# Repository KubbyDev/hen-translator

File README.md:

# Hen Translator

The goal of this project is to make a small module that can be attached around the neck of a chicken. This module listens for chicken sounds and "translates" them (it says a random sentence with a synthesized voice).
This idea is dumb, I know, but I learned a lot doing it.

## Demo

## Things I should change

- The main problem in this design is the lack of some kind of sound recognition. Just looking at the sound level is not enough to trigger the translation only when the chicken makes noises. I originally planned to try to use FFTs to make a simple recognition system but the AtMega328p is too underpowered and has far too little memory to work with. If I make a V2, I will probably go for a much more powerful STM32 or even a Linux system.
- The speaker is not powerful enough. This should be fairly easy to change but I have to keep in mind that it will also draw more power.

## How does it work?

### Electronics

I made my own PCB for this project. The main concerns when selecting the components were size, power consumption and cost.
All the components I used on the final board are listed here:
<https://github.com/KubbyDev/hen-translator/blob/main/Infos/Components.txt>

##### Storage

To store all the audio samples, I decided to use an SD card because it's easy to load new wave files. I used a mosfet to cut power when the SD card is not needed because the board is just listening most of the time.

##### Speaker

I used a simple 8 Ohm 0.7 Watt smd speaker to produce sounds. I added a large capacitor to filter out current spikes and a mosfet so the microcontroller can control it without powering it.

##### Microcontroller

At the beginning of the project I wanted to use an Arduino Nano because I was familiar with these boards. The main problem was its size. But then I heard about the Pro Mini which is much smaller. The only catch is that it doesn't have a USB port for programming, but it's not that hard to do without. Then I did some research and saw that it's a good idea to desolder the power led and the 3.3V LDO if I don't use them because they draw power. Ok why not. But then it's easier to just buy the microcontroller and solder it into my own board. The only difficulty it adds is the bootloader that doesn't come preinstalled.

So I chose an AtMega328p, and I added through-hole test points to plug wires to burn the bootloader (SPI) and load programs (Serial). I also added a switch between the power pins of the MCU and the power rail of the rest of the board because it's 3.3V and I want to be able to program it with an Arduino (5V) without putting 5V in the 3.3V components.

My first attempt at burning the bootloader didn't work because I was using the Arduino Uno bootloader but the 1st version of the PCB was using a 10 MHz crystal oscillator. This didn't cause problems to burn the bootloader because SPI is synchronous, but then I couldn't upload sketches because the baud rates were wrong. I solved this by simply using the 8 MHz internal clock instead of my 10 MHz external crystal, and burning a bootloader made for an 8 MHz clock. I could hack a 10 MHz bootloader but now that I know the external crystal is not needed, I prefer just removing it.

##### Power management

My first idea was to use a 3V button battery and a boost converter to get 5V to power the microcontroller. But I wanted to use an SD card which works at 3.3V, so I had to add a 3.3V LDO from 5V or a second boost converter. This is not efficient at all.
But then I saw that the AtMega328p works from 1.8V to 5.5V, so I decided to use a single boost converter to 3.3V and power everything from it. I also did some research about low voltage mode (1.8V) on SD cards but didn't find much information and it seemed like I would still have to start at 3.3V to then switch to 1.8V so I gave up this idea.

Later I realized I had another problem: the speaker draws 200 mA at 3.3V which a button battery can't provide. So I switched to a 1.5V AAA battery. But 200mA is also too much for the cheap boost converter I had found, and better boost converters are a lot more expensive. So I just connected the speaker directly to the battery so I don't need to change the converter (I had already ordered it), I can remove the resistor I had to limit current at 3.3V and I can have a higher current than if I chose a cheap regulator that I would have to run at its limits (so with a low efficiency). With this solution I get 0.3W at 1.5V.

I could switch to two 1/2 AAA 1.2V batteries. They take the same space as the 1.5V battery but have a combined output of 2.4V which forces 0.7W to pass through the speaker. But they are very expensive and the small increase in volume is not worth it.

##### Crystal oscillator

To provide a clock to the microcontroller I wanted to use a 16 MHz quartz oscillator at first because it's what's used on Uno and Nano boards. But when I chose to power everything from 3.3V I saw that the AtMega328p has a maximum clock speed that depends on the power input voltage. At 3.3V, 16 MHz is too fast, but 10 MHz should work fine so I used a 10 MHz external oscillator.

Then, because of the bootloader problems described in the microcontroller section, I just removed it to use the internal 8 MHz oscillator.

##### Microphone

I chose a MEMS microphone because they are cheap and very small. For the first version of the PCB I chose a PDM microphone without doing much research about it and found out later that it's very hard to read PDM from an AtMega328p...

I did a lot of research and found solutions like hacking the SPI controller to read PDM with it, using a DAC to convert PDM to analog to read it, using a low pass filter to filter out low SPL values and just triggering the translation when something comes out of the filter etc...

Eventually I just changed the PDM microphone for an analog output microphone with an operational amplifier. It was a nightmare to solder but it works well.

##### PCB

The first PCB had some major flaws like the microphone I couldn't read, the speaker that drew too much current and some pullup resistors that were missing on the SPI lines for the SD card. I also connected Aref to VCC instead of a capacitor to GND on the microcontroller.

The test points were too small for my wires, so I had to solder them but some of the vias detached and everything was a big mess, but I was able to learn from it and I haven't had any problem with the second version of the PCB.

### Software

To burn the bootloader, I use an Arduino Uno with the ArduinoISP example sketch connected via SPI to my PCB. To upload sketches, I use an Arduino Uno with the microcontroller removed and a Serial connection to my PCB. The procedure is detailed here:
<https://github.com/KubbyDev/hen-translator/blob/main/Infos/BurnBootloader.txt>

The program has 3 things to do:

- listen for chicken sounds
- when it detects one, play a random wav file from the SD card
- monitor the battery voltage and alert with the led or the speaker when power is too low

##### Speaker control

To play wav files I use the TMRpcm library. It's easy to use because my use case is standard.

##### SD card reading

To read data from the SD card I use the Arduino SD library (and TMRpcm does too). It works with standard 2GB SD cards but not with the cheap 512B cards I bought. I will try to fix the library but for now I just use 2GB cards.

##### Microphone reading

I would like to do some cool FFT sound recognition but I don't think it will be possible on the AtMega328p mainly because it's too slow and doesn't have enough ram.
For the moment I will just trigger the translation when the sound pressure level goes higher than a certain threshold.

### Mechanics

I had to learn Fusion360 for this project so the CAD could probably be way better, but it works.
There are two parts. The box that goes on the chicken, and a stand because I don't actually have a chicken at home and also because this version is not reliable enough for these conditions.
Everything is 3D printed in white PLA and painted.

The collar is just a box holding the board and the battery with a power switch and holes for sound to come in and out.

The stand is based on a chicken I found on Thingyverse. The interior is hollow, and contains a PCB (the same PCB, but without microphone because it's not needed), a battery, a power switch and a button to trigger a chicken sound. The button is an end of travel sensor that we can trigger by pushing on the thingy on the head of the chicken.

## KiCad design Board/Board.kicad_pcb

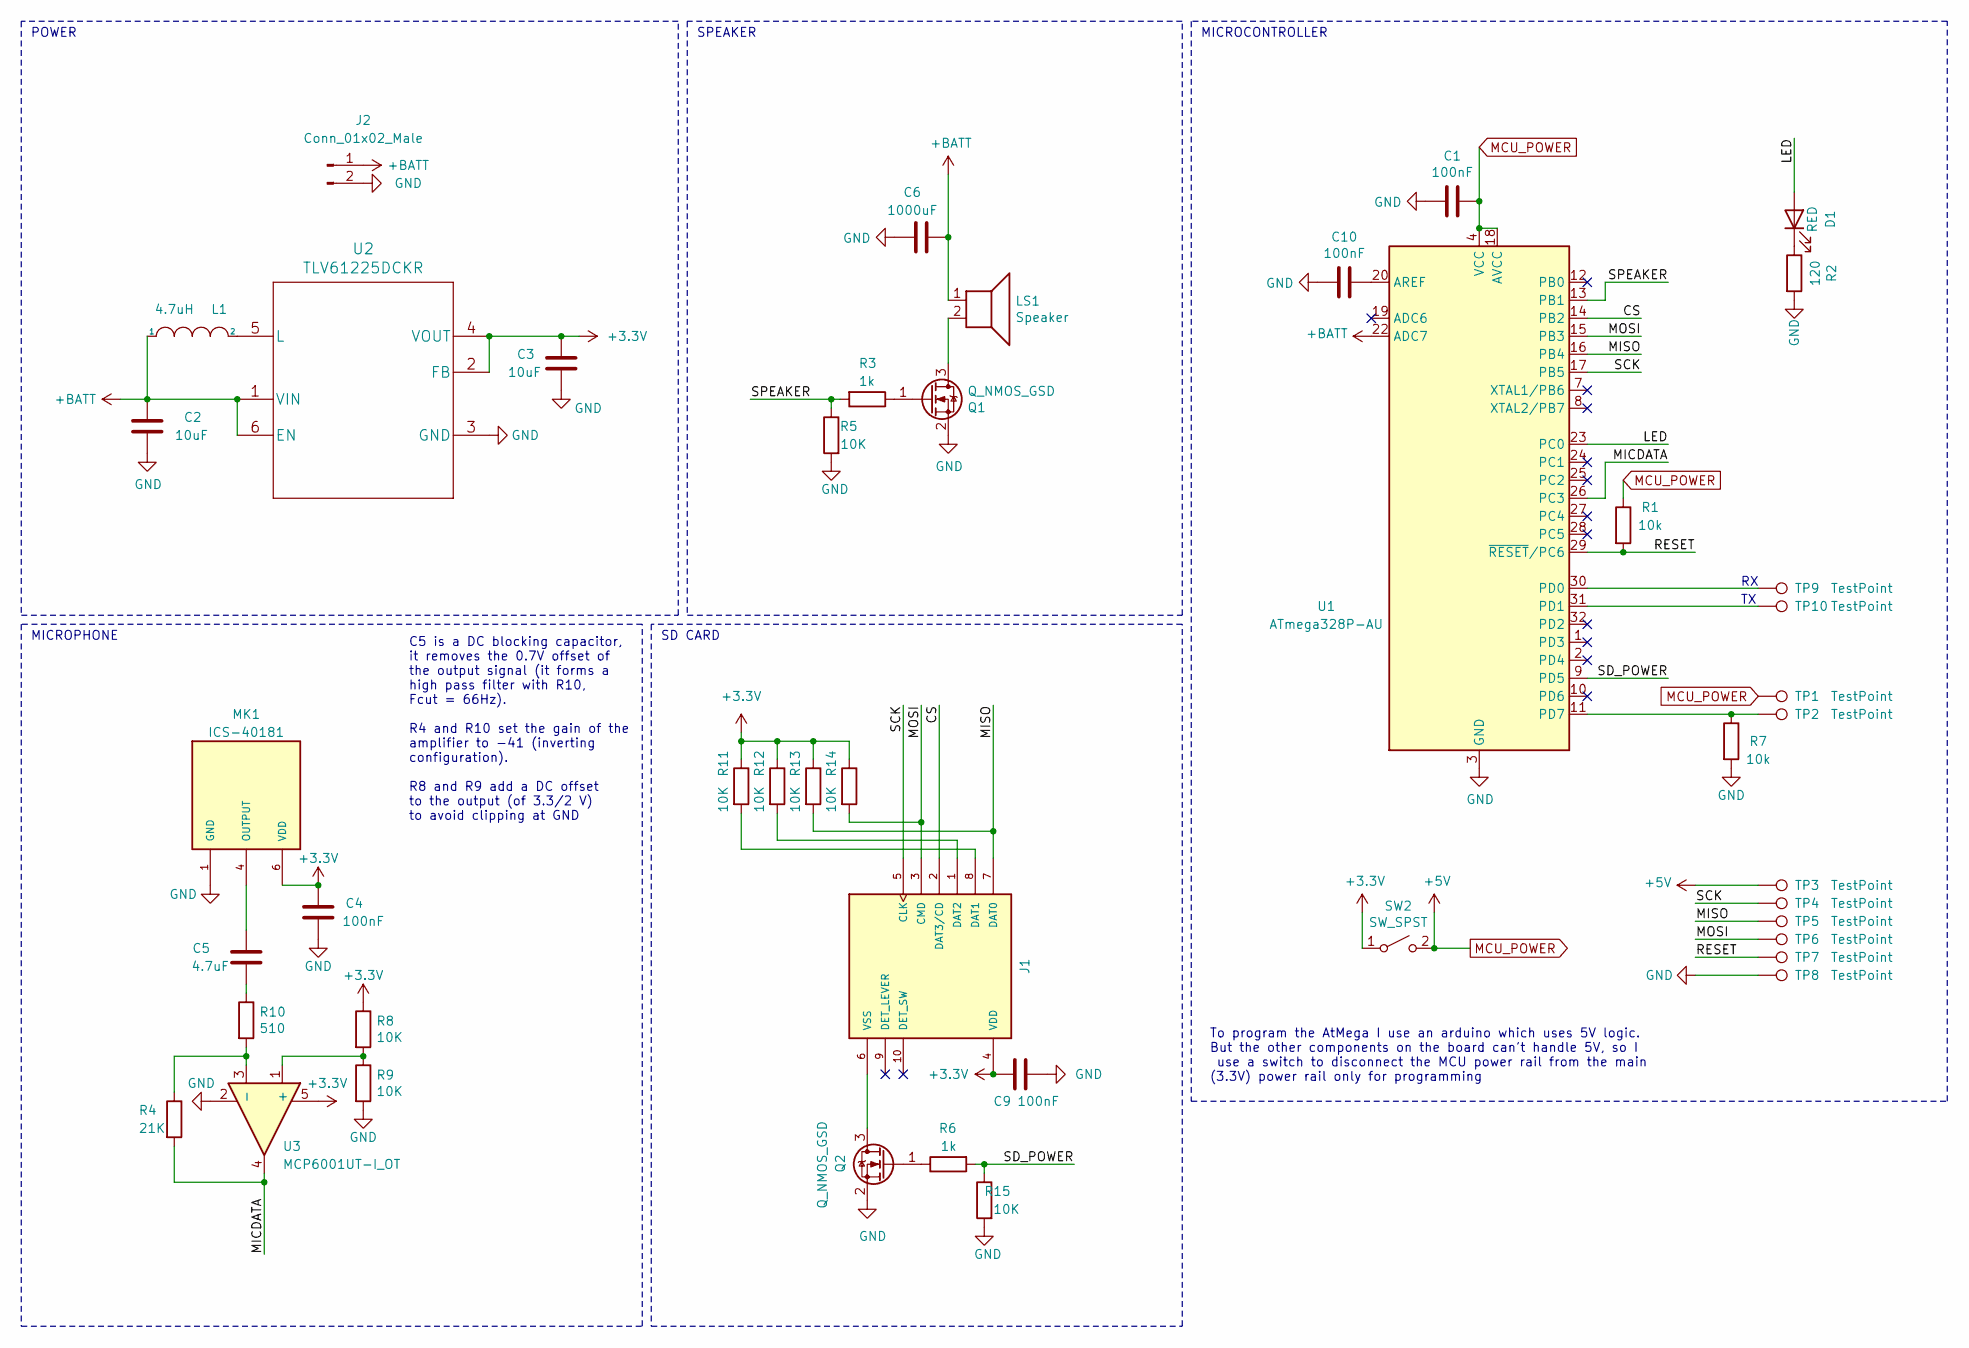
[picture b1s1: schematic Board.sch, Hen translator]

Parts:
C1, C4, C9, C10: 100nF; C_0603_1608Metric
C2, C3: 10uF; C_0805_2012Metric
C5: 4.7uF; C_0603_1608Metric
C6: 1000uF; C_Radial_D8.0mm_H11.5mm_P3.50mm
D1: RED; LED_0805_2012Metric
J1: 5025700893; MOLEX_5025700893
J2: Conn_01x02_Male; S02B-PASK
L1: 4.7uH; L_1008_2520Metric
LS1: Speaker; SPKR_CMS-151135-078S-67
MK1: ICS-40181; MIC_ICS-40181
Q1, Q2: Q_NMOS_GSD; SOT-23
R1, R7: 10k; R_0603_1608Metric
R2: 120; R_0603_1608Metric
R3, R6: 1k; R_0603_1608Metric
R4: 21K; R_0603_1608Metric
R5, R8, R9, R11, R12, R13, R14, R15: 10K; R_0603_1608Metric
R10: 510; R_0603_1608Metric
SW2: SW_SPST; SW_DIP_SPSTx01_Slide_6.7x4.1mm_W7.62mm_P2.54mm_LowProfile
TP1, TP2, TP3, TP4, TP5, TP6, TP7, TP8, TP9, TP10: TestPoint; TestPoint_THTPad_D1.0mm_Drill0.7mm
U1: ATmega328P-AU; TQFP-32_7x7mm_P0.8mm
U2: TLV61225DCKR; SOT65P210X110-6N
U3: MCP6001UT-I_OT; SOT95P270X145-5N

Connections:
+3V3: C3.1, C4.1, C9.1, J1.4 (VDD), MK1.6 (VDD), R8.1, R11.1, R12.1, R13.1, R14.1, SW2.1 (A), U2.2 (FB), U2.4 (VOUT), U3.5
+BATT: C2.1, C6.1, J2.1, L1.1, LS1.1, U1.22 (ADC7), U2.1 (VIN), U2.6 (EN)
/CS: J1.2 (DAT3/CD), U1.14 (PB2)
/LED: D1.2 (A), U1.23 (PC0)
/MICDATA: R4.2, U1.26 (PC3), U3.4
/MISO: J1.7 (DAT0), R13.2, TP5.1, U1.16 (PB4)
/MOSI: J1.3 (CMD), R14.2, TP6.1, U1.15 (PB3)
/RESET: R1.2, TP7.1, U1.29 (~RESET~/PC6)
/SCK: J1.5 (CLK), TP4.1, U1.17 (PB5)
/SD_POWER: R6.2, R15.1, U1.9 (PD5)
/SPEAKER: R3.2, R5.1, U1.13 (PB1)
GND: C1.2, C2.2, C3.2, C4.2, C6.2, C9.2, C10.2, J2.2, MK1.1 (GND), MK1.2 (GND), MK1.3 (GND), MK1.5 (GND), Q1.2 (S), Q2.2 (S), R2.2, R5.2, R7.2, R9.2, R15.2, TP8.1, U1.3 (GND), U1.5 (GND), U1.21 (GND), U2.3 (GND), U3.2
MCU_POWER: C1.1, R1.1, SW2.2 (B), TP1.1, TP3.1, U1.4 (VCC), U1.6 (VCC), U1.18 (AVCC)
unnamed: C5.1, MK1.4 (OUTPUT)
unnamed: C5.2, R10.1
unnamed: C10.1, U1.20 (AREF)
unnamed: D1.1 (K), R2.1
unnamed: J1.1 (DAT2), R12.2
unnamed: J1.6 (VSS), Q2.3 (D)
unnamed: J1.8 (DAT1), R11.2
unnamed: L1.2, U2.5 (L)
unnamed: LS1.2, Q1.3 (D)
unnamed: Q1.1 (G), R3.1
unnamed: Q2.1 (G), R6.1
unnamed: R7.1, TP2.1, U1.11 (PD7)
unnamed: R8.2, R9.1, U3.1 (+)
unnamed: R4.1, R10.2, U3.3 (-)
unnamed: TP9.1, U1.30 (PD0)
unnamed: TP10.1, U1.31 (PD1)

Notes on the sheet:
POWER
SD CARD
MICROPHONE
SPEAKER
MICROCONTROLLER
C5 is a DC blocking capacitor, it removes the 0.7V offset of the output signal (it forms a high pass filter with R10, Fcut = 66Hz). R4 and R10 set the gain of the amplifier to -41 (inverting configuration). R8 and R9 add a DC offset to the output (of 3.3/2 V) to avoid clipping at GND
To program the AtMega I use an arduino which uses 5V logic. But the other components on the board can't handle 5V, so I use a switch to disconnect the MCU power rail from the main (3.3V) power rail only for programming

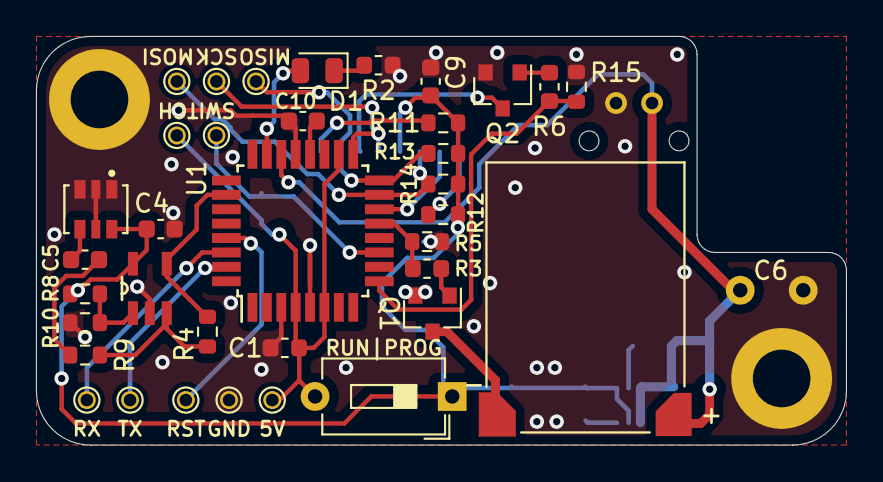
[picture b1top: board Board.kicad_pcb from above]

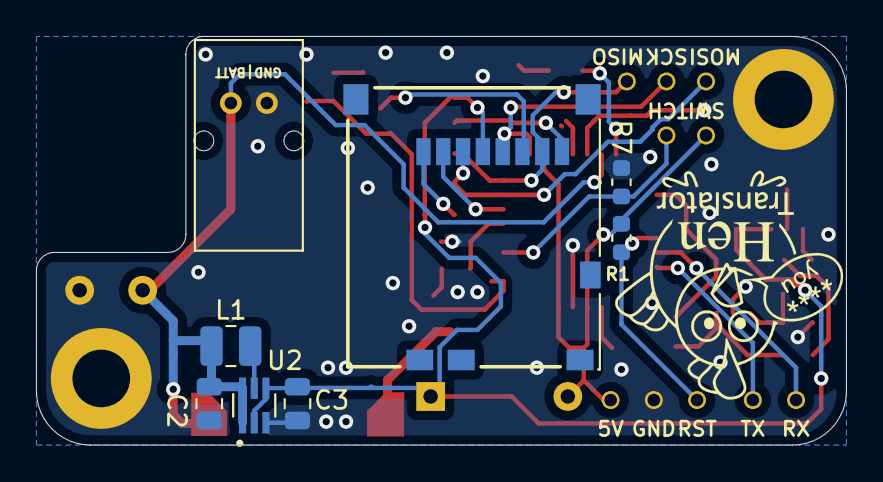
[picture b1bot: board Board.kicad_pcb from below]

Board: 2 copper layers, 45.0 x 22.7 mm, 45 parts (8 on the bottom side), 29 nets.

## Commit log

2021-01-24 Some research
2021-01-25 Switched to 3.3V
2021-01-26 Started schematic
2021-01-29 Schematic and BOM almost done
2021-02-05 Schematic done, components almost selected
2021-02-07 BOM ready
2021-02-07 Changed components + first layout tests
2021-02-09 First PCB
2021-02-09 PCB almost done
2021-02-09 Replaced SD connector by correct one
2021-02-10 Started enclosure
2021-02-10 Board done :)
2021-02-18 Enclosure almost finished
2021-02-25 Enclosure added handles
2021-02-25 Fourrier tests
2021-03-09 Started hardware tests
2021-03-10 Board V1.1: ARef fix
2021-03-13 Speaker and AnalogRead tests
2021-03-13 Bootloader and program loading procedures
2021-03-14 Enclosure ready for print
2021-03-15 Started stand CAD
2021-03-15 Microphone research + BatteryReading and SDcard tests improvements
2021-03-15 Minor improvements
2021-03-17 Better sound holes
2021-03-27 New microphone circuit
2021-03-30 PCB v1.1 done
2021-03-31 PCB v1.1 ready
2021-03-31 Low level tests for v1.1
2021-04-01 Minor enclosure fixes
2021-04-02 Added Gate pulldowns
2021-04-11 Started Chicken CAD
2021-04-15 Chicken CAD Done
2021-04-15 Software fixes
2021-04-21 Software POCs almost done
2021-04-24 All POCs done, but sound really low
2021-04-26 First version of the readme
2021-04-26 Added PCB picture
2021-04-27 Fixed low sound problem
2021-04-28 Started main program
2021-04-30 Added demo
2021-05-02 Software done
2021-05-02 Stand done
2021-11-14 Fix threshold values
